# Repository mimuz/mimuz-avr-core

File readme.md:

# mi:muz avr-core

`mi:muz avr-core`はATtiny向けのArduino用MIDIライブラリです。

------

## Arduino Library

Arduinoを使ってMIDIで遊ぶためのATtinyにMIDI機能を追加するライブラリとArduino IDE 1.6.3向けの設定ファイル。

- [VUSB-MIDI-ATtiny](./arduino/libraries/VUSBMidiATtiny)（ATtinyでUSB-MIDIデバイスを作るためのArduinoライブラリ）
- [ArduinoIDE 1.6.3向け設定ファイル](./arduino/hardware)（Arduino IDEにmi:muzボード設定を追加するファイル）
- [Hybrid MIDI for mi:muz:expr](./arduino/libraries/HybridMidiAttiny) (mi:muz:exprボード用のArduinoライブラリ。V-USBとI2C Slaveの両方に対応したMIDIデバイスが作れます)

## boards

mi:muz avr-coreに対応したボードの回路図とサンプルコードです

### mi:muz ATtiny Boards (protシリーズ)

ATtinyを搭載しV-USB MIDIを使ったMIDIデバイスを簡単に作るための実験用ボード。

- [mi:muz:prot#1](./boards/prot1)（ATtiny45/85用V-USB-MIDI実験用ボード）
- [mi:muz:prot#2](./boards/prot2)（ATtiny44/84/841用V-USB-MIDI実験用ボード）
- [mi:muz:prot#3](./boards/prot3)（ATtiny45/85用V-USB-MIDI実験用ボード。I2Cマスタ用回路入り）

### mi:muz ATtiny Boards (exprシリーズ)

ATtinyを搭載しHybrid MIDIに対応したMIDIデバイスを簡単に作るための実験用ボード。
Arduinoと複数のexprシリーズボードを組み合わせた実験が行いたいときはこちら。

- [mi:muz:expr#1](./boards/expr1)（ATtiny85用Hybrid-MIDI実験用ボード）
- [mi:muz:expr#2](./boards/expr2)（ATtiny841用Hybrid-MIDI実験用ボード）

### Arduinoシールド

mi:muzを有効活用するためのArduino UNO用シールド。

- [mi:muz:wrtr](./boards/wrtr)（8/14ピンATtiny向けの小さなISPシールド）
- [mi:muz:mstr-uno](./boards/mstr-uno) (mi:muz:exprをArduino UNOに接続するためのシールド)

### mi:muz ATtinyボード用アタッチメント

mi:muz ATtinyボードを使って簡単にデバイスの実験を行うためのアタッチメント。

- [mi:muz:sndr#1](./boards/sndr1)（mi:muz:expr#1,#2用オーディオアダプタ）
- [mi:muz:ctlr#1](./boards/ctlr1)（mi:muz:expr#2用 8chコントローラーアダプタ）

# Applications

`mi:muz`プロジェクトで生まれたデバイスを紹介しています。

- [フィジカルWebアプリ「ち〜ん」](http://qiita.com/tadfmac/items/702e74efad1dd606166a)（MIDIデバイス化した呼び鈴と連携するWebアプリ）
- [mi:muz:can (旧名：can attacker (缶たたくやつ))](https://github.com/mimuz/mimuz-can)
- [mi:muz:tuch](https://github.com/mimuz/mimuz-tuch) MIDI Controller with flexible touch keys.

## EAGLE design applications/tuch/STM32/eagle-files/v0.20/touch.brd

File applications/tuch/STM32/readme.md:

# mi:muz:tuch (MIDI Controller with flexible touch keys) STM32 Version

mi:muz:tuch is a USB MIDI controller with capacitive touch sensor.
It has now two indivisual versions, AVR or STM32.

And also, Web preset configurator is available to [Configurator](http://mz4u.net/tuch/).
MIDI note numbers be able to change to You want.  

# STM32 Version (STM32F042K6T6)

STM32 version of mi:muz:tuch (v0.2x) is my first STM32 project, it now only support USB Mode.

## Version

- v0.20 (2016.08.27)

## Known Issues

- v0.20 does not support I2C Slave Mode.

## Schematic

## Top View

## Eagle Files

[eagle files (v0.20)](./eagle-files/v0.20)

## parts

- [STM32F042K6T6](http://www.st.com/content/st_com/ja/products/microcontrollers/stm32-32-bit-arm-cortex-mcus/stm32f0-series/stm32f0x2/stm32f042k6.html) * 1
- [Ferrite beads](http://akizukidenshi.com/catalog/g/gP-04054/) * 2 [ID1,ID2]
- 470Ω(0603) * 1 (For USB DATA LED)
- 1kΩ(0603) * 6 (For touch line LED)
- 1.5kΩ(0603) * 1 (D+ Line Pull up)
- 10kΩ(0603) * 1 (Tactical switch pull down)
- 1MΩ(2012) * 6 (For Touch Sensor)
- 3mLED * 7 
- 0.1uF(0603) * 4
- 22uF(0805) * 1
- [Tactical Switch (4 points SMT 4.5mm)](http://www.aitendo.com/product/7047) * 1
- [Tactical Switch (2 points SMT)](http://www.aitendo.com/product/10525) * 1

## Firmware

- [Source](./source)
- [bin](./bin)

### Firmware Setup 

1. Install [SW4STM32](http://www.st.com/content/st_com/ja/products/development-tools/software-development-tools/stm32-software-development-tools/stm32-ides/sw4stm32.html)
2. Install DFU Loader (i.e. dfu-util see [dfu-util - Device Firmware Upgrade Utilities](http://dfu-util.sourceforge.net/))
2. Copy [Source](./source/mimuz-tuch) to your workspace path and Bulding Software
3. Connect mi:muz:tuch board with holding push to 'BOOT0' Switch to USB Port
4. Burn [mimuz-tuch.bin] using DFU Loader. On Mac, enter the following command on shell in same mimuz-tuch.bin path.

> `dfu-util -a0 -d 0x0483:0xdf11 -s 0x008000000 -D mimuz-tuch.bin`

# Licenses

## Hardware (Schematics, Board, Eagle files), Software (Application, USB-MIDI Class Driver)

- [Creative Commons Attribution 4.0 International (CC BY 4.0)](http://creativecommons.org/licenses/by/4.0/)

## Software (STMCube from ST Microsystems)

- 3-clause BSD license

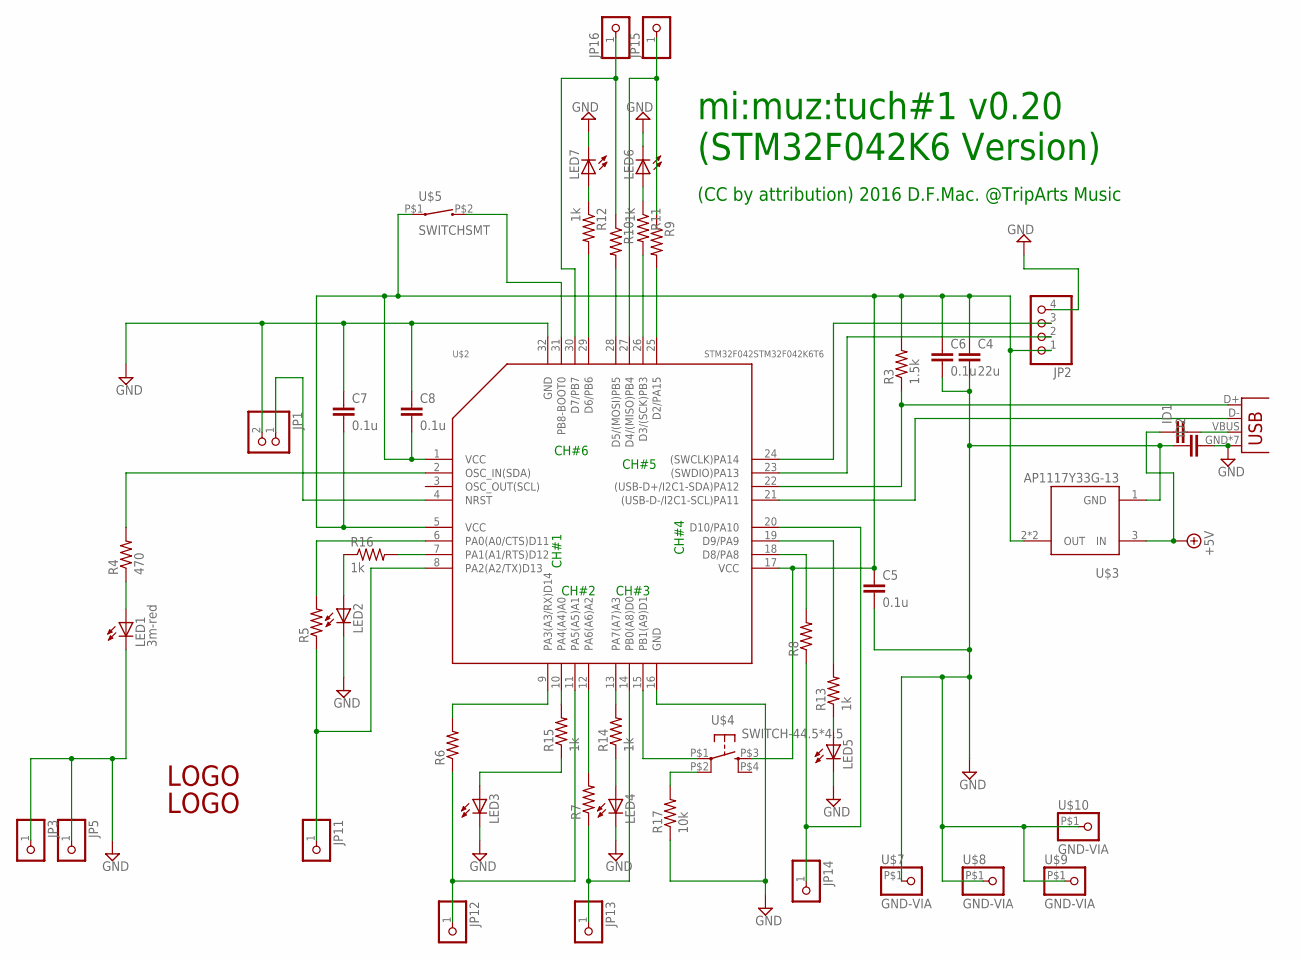
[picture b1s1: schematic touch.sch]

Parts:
C4: 22u; C0805
C5, C6, C7, C8: 0.1u; C0603
ID1, ID2: C-EUC0805; C0805
JP1: PINHD-1X2; 1X02
JP2: PINHD-1X4; 1X04
JP3, JP5: PINHD-1X13MM; 1X01
JP4: USB-MICROB
JP11, JP12, JP13, JP14, JP15, JP16: PINHD-1X15MM; 1X01-LARGE
LED1: 3m-red; LED3MM
LED2, LED3, LED4, LED5, LED6, LED7: LED3MM
R3: 1.5k; R0603
R4: 470; R0603
R5, R6, R7, R8, R9, R10: R-US_R0805; R0805
R11, R12, R13, R14, R15, R16: 1k; R0603
R17: 10k; R0603
U$1, U$6: LOGOSMALL; LOGO-SMALL
U$2: STM32F042STM32F042K6T6; TQFP32
U$3: AP1117Y33G-13; SOT89
U$4: SWITCH-44.5*4.5; SWITCH-SMT-4.5*4.5
U$5: SWITCHSMT; SWITCH-SMT-2*4*3
U$7, U$8, U$9, U$10: GND-VIA

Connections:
+5V: ID1.1, U$3.3 (IN)
D+: JP4.D+, R3.1, U$2.22 ((USB-D+/I2C1-SDA)PA12)
D-: JP4.D-, U$2.21 ((USB-D-/I2C1-SCL)PA11)
GND: C4.2, C5.2, C6.2, C7.1, C8.1, ID2.1, ID2.2, JP1.2, JP2.4, JP3.1, JP4.GND, JP4.MT1 (GND), JP4.MT3 (GND), JP4.P$2 (GND), JP4.P$4 (GND), JP4.P$5 (GND), JP4.P$6 (GND), JP5.1, LED1.K (C), LED2.K (C), LED3.K (C), LED4.K (C), LED5.K (C), LED6.K (C), LED7.K (C), R17.1, U$2.16 (GND), U$2.32 (GND), U$3.1 (GND), U$7.P$1, U$8.P$1, U$9.P$1, U$10.P$1
unnamed: R5.2, U$2.6 (PA0(A0/CTS)D11)
unnamed: R4.2, U$2.2 (OSC_IN(SDA))
unnamed: R15.2, U$2.10 (PA4(A4)A0)
unnamed: R16.2, U$2.7 (PA1(A1/RTS)D12)
unnamed: LED3.A, R15.1
unnamed: LED1.A, R4.1
unnamed: R14.2, U$2.13 (PA7(A7)A3)
unnamed: R17.2, U$4.P$2 (P1)
unnamed: JP11.1, R5.1, U$2.8 (PA2(A2/TX)D13)
unnamed: R6.2, U$2.9 (PA3(A3/RX)D14)
unnamed: R8.2, U$2.18 (D8/PA8)
unnamed: R13.2, U$2.19 (D9/PA9)
unnamed: R7.2, U$2.12 (PA6(A6)A2)
unnamed: R9.2, U$2.25 (D2/PA15)
unnamed: C4.1, C5.1, C6.1, C7.2, C8.2, JP2.1, R3.2, U$2.1 (VCC), U$2.5 (VCC), U$2.17 (VCC), U$3.2 (OUT), U$3.2@1 (OUT), U$4.P$3 (S), U$5.P$1 (1)
unnamed: R11.2, U$2.26 (D3/(SCK)PB3)
unnamed: R10.2, U$2.28 (D5/(MOSI)PB5)
unnamed: R12.2, U$2.29 (D6/PB6)
unnamed: U$2.15 (PB1(A9)D1), U$4.P$1
unnamed: LED2.A, R16.1
unnamed: LED7.A, R12.1
unnamed: LED6.A, R11.1
unnamed: LED4.A, R14.1
unnamed: LED5.A, R13.1
unnamed: JP2.3, U$2.24 ((SWCLK)PA14)
unnamed: JP2.2, U$2.23 ((SWDIO)PA13)
unnamed: JP1.1, U$2.4 (NRST)
unnamed: U$2.31 (PB8-BOOT0), U$5.P$2 (2)
unnamed: JP12.1, R6.1, U$2.11 (PA5(A5)A1)
unnamed: JP13.1, R7.1, U$2.14 (PB0(A8)D0)
unnamed: JP14.1, R8.1, U$2.20 (D10/PA10)
unnamed: JP15.1, R9.1, U$2.27 (D4/(MISO)PB4)
unnamed: JP16.1, R10.1, U$2.30 (D7/PB7)
VBUS: ID1.2, JP4.VBUS

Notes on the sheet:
mi:muz:tuch#1 v0.20 (STM32F042K6 Version)
(CC by attribution) 2016 D.F.Mac. @TripArts Music
CH#1
CH#2
CH#3
CH#4
CH#5
CH#6

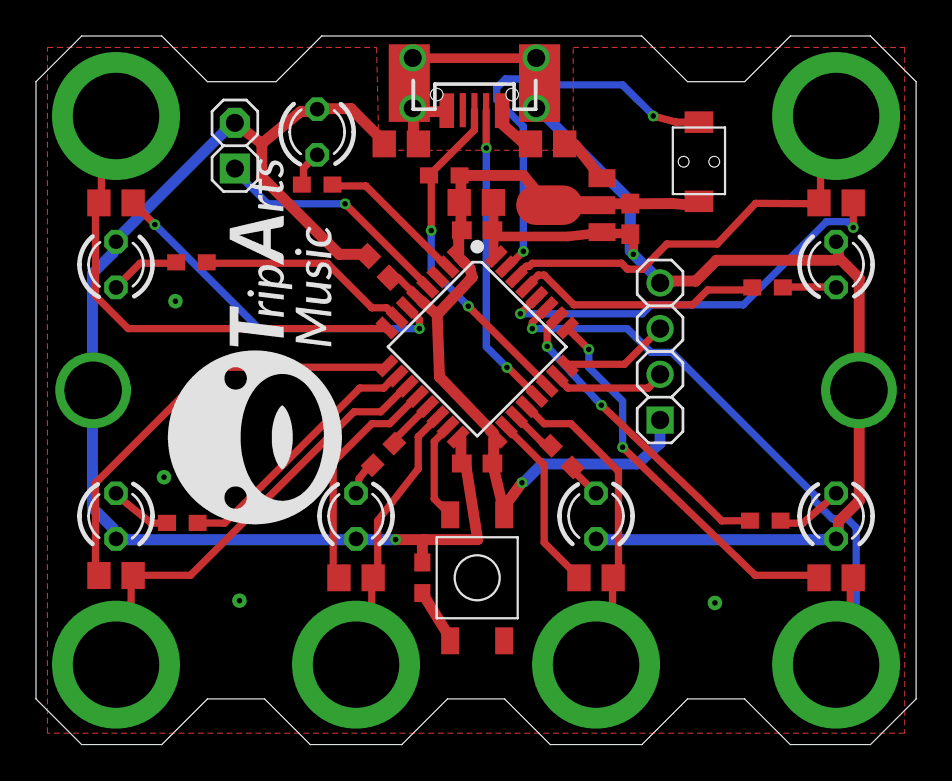
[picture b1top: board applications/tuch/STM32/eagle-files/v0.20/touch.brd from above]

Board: 2 copper layers, 48.9 x 39.4 mm, 50 parts (1 on the bottom side), 38 nets.

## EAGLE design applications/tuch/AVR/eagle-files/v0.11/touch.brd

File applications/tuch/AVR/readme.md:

# mi:muz:tuch (MIDI Controller with flexible touch keys) AVR Version

mi:muz:tuch is a USB MIDI controller with capacitive touch sensor.
It has now two indivisual versions, AVR or STM32.

And also, Web preset configurator is available to [Configurator](http://mz4u.net/tuch/).
MIDI note numbers be able to change to You want.  

# AVR Version (ATtiny44 16Mhz with ATmega8A 8Mhz)

AVR version of mi:muz:tuch (v0.1x) is based mi:muz:expr#2 for 'Hybrid MIDI feature, It can be able to connect to PC's USB Port using V-USB or mi:muz:mstr (I2C master) devices's I2C port using I2C slave mode.

## Version

- v0.11 (2016.07.31)

## Known Issues

- v0.1x does not work properly when connected to a USB2.0 Hub. (V-USB's general issue... unfixable...)
- [v0.1x does not work USB Mode when ch#6 is enable.] (https://github.com/tadfmac/mi-muz/issues/4)

## Schematic

## Top View

## Bottom View

## Eagle Files

[eagle files (v0.11)](./eagle-files/v0.11)

## parts

- [ATtiny44A-SSU](http://www.atmel.com/ja/jp/devices/ATTINY44A.aspx) * 1
- [ATmega8A-AU](http://www.atmel.com/ja/jp/devices/ATMEGA8A.aspx) * 1
- Zener diode(SOD323) 3.6V * 2
- Crystal 16Mhz (5032 2Pad) * 1
- [Ferrite beads](http://akizukidenshi.com/catalog/g/gP-04054/) * 2 [ID1,ID2]
- 100Ω(0603) * 2 (For USB D+, D- Line)
- 470Ω(0603) * 1 (For ATtiny44 LED)
- 1kΩ(0603) * 6 (For ATmega8A touch line LED)
- 4.7kΩ(0603) * 1 (D- Line Pull up)
- 10kΩ(0603) * 1 (Tactical switch pull down)
- 1MΩ(2012) * 6 (For Touch Sensor)
- 3mLED * 7 
- 22pF(0603) * 2
- 0.1uF(0603) * 5
- 22uF(0805) * 1
- [Switch](http://akizukidenshi.com/catalog/g/gP-03651/) * 1
- Pin headers (2.54mm) 2×3 * 2
  WARNING: if you have v0.1 board, it has a bug that missing junction from ATmega8A to ISP.

## sketches

- [Touch Sensor (for ATmega8A)](https://github.com/tadfmac/mi-muz/tree/master/applications/tuch/sketch/mega8_touchSensor/)
- [Touch Sensor to Hybrid MIDI bridge (for ATtiny44A)](https://github.com/tadfmac/mi-muz/tree/master/applications/tuch/sketch/mimuz-tuch_v01/)

# Licenses

## Hardware (Schematics), Configurator

[Creative Commons Attribution 4.0 International (CC BY 4.0)](http://creativecommons.org/licenses/by/4.0/)

## Software (Sketches/Libraries)

[GNU General Public License, version 2 (GPL-2.0)](http://opensource.org/licenses/gpl-2.0.php).

See lso [HybridMidiAttiny](https://github.com/tadfmac/mi-muz/tree/master/arduino/libraries/HybridMidiAttiny).

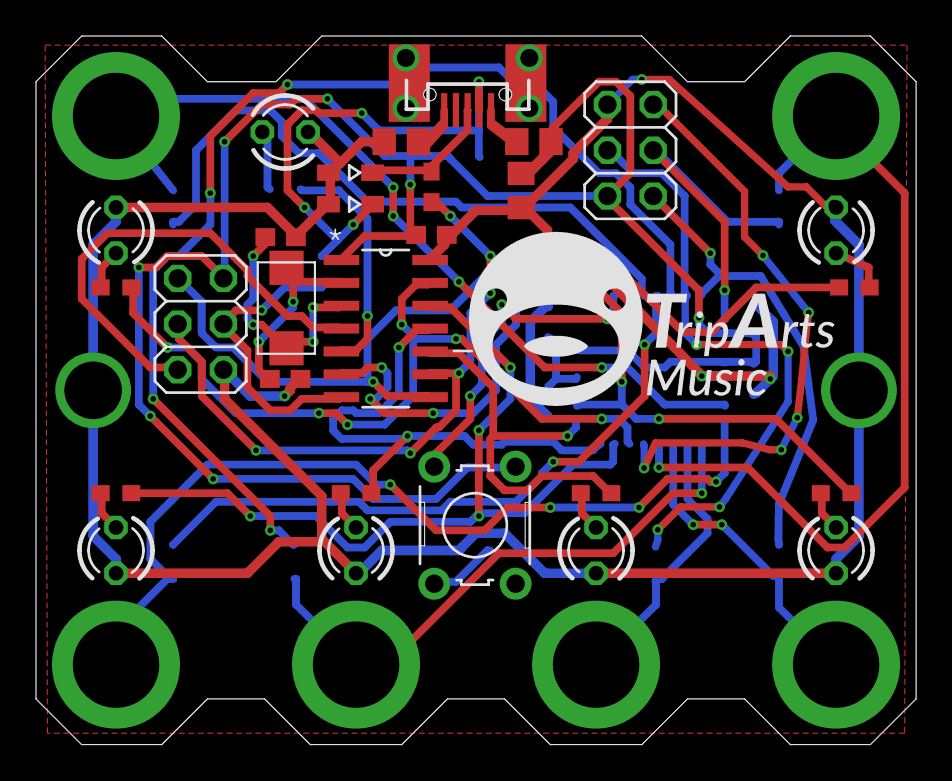
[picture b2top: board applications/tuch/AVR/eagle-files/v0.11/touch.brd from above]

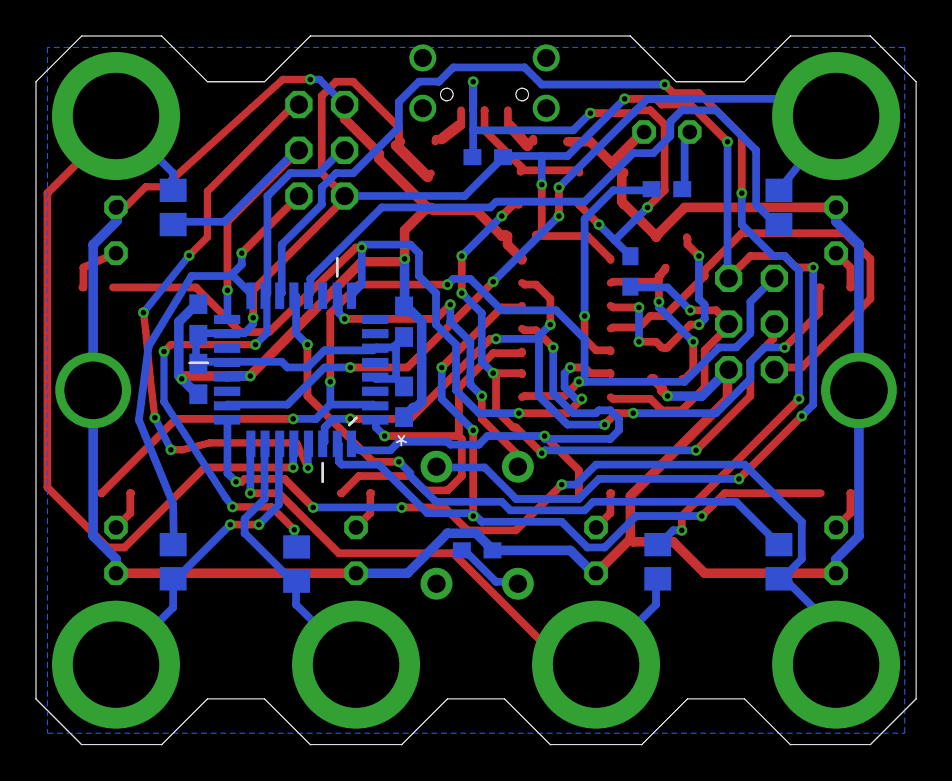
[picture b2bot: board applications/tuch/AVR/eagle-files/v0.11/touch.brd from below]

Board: 2 copper layers, 48.9 x 39.4 mm, 52 parts (15 on the bottom side), 40 nets.

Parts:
C1, C5, C6, C7, C8: 0.1u; C0603
C2, C3: 22p; C0603
C4: 22u; C0805
ID1, ID2: C0805
JP1, JP2: 2X03
JP3, JP5: 1X01
JP4: USB-MICROB
JP11, JP12, JP13, JP14, JP15, JP16: 1X01-LARGE
LED1: 3m-red; LED3MM
LED2, LED3, LED4, LED5, LED6, LED7: LED3MM
Q1: MC-405
R1, R2, R17: 75; R0603
R3: 1.5k; R0603
R4, R11, R12, R13, R14, R15, R16: 470; R0603
R5, R6, R7, R8, R9, R10: R0805
S1: B3F-10XX
U2: ATTINY44-20SSU; SOIC127P600X175-14N
U3: ATMEGA8A-AU; QFP80P900X900X120-32N
U$1: LOGOSMALL; LOGO-SMALL
ZD1, ZD2: 3.6V; SOD323-W

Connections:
+5V: C1.1, C4.1, C5.1, C6.1, C7.1, C8.1, ID1.1, JP1.2, JP2.2, R3.2, S1.1, U2.1, U3.4, U3.6, U3.18, U3.20
D+: JP4.D+, R2.2, ZD1.C
D-: JP4.D-, R1.2, R3.1, ZD2.C
GND: C1.2, C2.1, C3.1, C4.2, C5.2, C6.2, C7.2, C8.2, ID2.1, JP1.6, JP2.6, JP3.1, JP5.1, LED1.K, LED2.K, LED3.K, LED4.K, LED5.K, LED6.K, LED7.K, R17.1, U2.14, U3.21, ZD1.A, ZD2.A
GND1: ID2.2, JP4.GND
unnamed: R5.2, U3.12
unnamed: R4.2, U2.5
unnamed: C2.2, Q1.2, U2.2
unnamed: C3.2, Q1.1, U2.3
unnamed: R11.2, U2.13, U3.30
unnamed: LED1.A, R4.1
unnamed: R12.2, U2.12, U3.31
unnamed: R14.2, U2.10, U3.1
unnamed: JP11.1, R5.1, U3.23
unnamed: JP2.5, U2.4
unnamed: R13.2, U2.11, U3.32
unnamed: JP2.4, R1.1, U2.7
unnamed: R6.2, U3.13
unnamed: R17.2, S1.4
unnamed: R7.2, U3.14
unnamed: JP1.4, R8.2, U3.15
unnamed: JP1.5, U3.29
unnamed: JP1.1, R9.2, U3.16
unnamed: JP1.3, R10.2, U3.17
unnamed: LED7.A, R16.1
unnamed: LED6.A, R15.1
unnamed: LED5.A, R14.1
unnamed: LED4.A, R13.1
unnamed: LED3.A, R12.1
unnamed: LED2.A, R11.1
unnamed: R16.2, U2.6, U3.9
unnamed: JP12.1, R6.1, U3.24
unnamed: JP13.1, R7.1, U3.25
unnamed: JP14.1, R8.1, U3.26
unnamed: JP15.1, R9.1, U3.27
unnamed: JP16.1, R10.1, U3.28
unnamed: S1.3, U3.10
unnamed: JP2.3, R2.1, U2.9
unnamed: JP2.1, R15.2, U2.8, U3.2
VBUS: ID1.2, JP4.VBUS

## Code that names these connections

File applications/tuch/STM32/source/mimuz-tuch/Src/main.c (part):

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//
// PIN Configuration
//
// PA0 : CH#1 Sensor (OUT)
// PA1 : CH#1 LED    (OUT)
// PA2 : CH#1 Sensor (IN)
// PA3 : CH#2 Sensor (OUT)
// PA4 : CH#2 LED    (OUT)
// PA5 : CH#2 Sensor (IN)
// PA6 : CH#3 Sensor (OUT)
// PA7 : CH#3 LED    (OUT)
// PB0 : CH#3 Sensor (IN)
// PB1 : Calibration Button (IN)
// PA8 : CH#4 Sensor (OUT)
// PA9 : CH#4 LED    (OUT)
// PA10: CH#4 Sensor (IN)
// PA11: USB D-
// PA12: USB D+
// PA13: SWDIO
// PA14: SWCLK
// PA15: CH#5 Sensor (OUT)
// PB3 : CH#5 LED    (OUT)
// PB4 : CH#5 Sensor (IN)
// PB5 : CH#6 Sensor (OUT)
// PB6 : CH#6 LED    (OUT)
// PB7 : CH#6 Sensor (IN)
// PB8 : BOOT0
// PF0 : USB DATA LED (OUT)
// PF1 : N/A

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
// Tuch Sensor GPIO Table
TTouchGPIO ttouchGpio[TOUCH_CHANNELS]={
  {GPIOA, GPIOA, GPIOA, GPIO_PIN_0, GPIO_PIN_1, GPIO_PIN_2}, // PA0, PA1, PA2 (CH#1)
  {GPIOA, GPIOA, GPIOA, GPIO_PIN_3, GPIO_PIN_4, GPIO_PIN_5}, // PA3, PA4, PA5 (CH#2)
  {GPIOA, GPIOA, GPIOB, GPIO_PIN_6, GPIO_PIN_7, GPIO_PIN_0}, // PA6, PA7, PB0 (CH#3)
  {GPIOA, GPIOA, GPIOA, GPIO_PIN_8, GPIO_PIN_9, GPIO_PIN_10},// PA8, PA9, PA10(CH#4)
  {GPIOA, GPIOB, GPIOB, GPIO_PIN_15,GPIO_PIN_3, GPIO_PIN_4}, // PA15,PB3, PB4 (CH#5)
  {GPIOB, GPIOB, GPIOB, GPIO_PIN_5, GPIO_PIN_6, GPIO_PIN_7}  // PB5, PB6, PB7 (CH#6)
};

void sensorLEDOn(int ch){
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

// GPIO PIN Configuration
// PA0 : CH#1 Sensor (OUT)
// PA1 : CH#1 LED    (OUT)
// PA2 : CH#1 Sensor (IN)
// PA3 : CH#2 Sensor (OUT)
// PA4 : CH#2 LED    (OUT)
// PA5 : CH#2 Sensor (IN)
// PA6 : CH#3 Sensor (OUT)
// PA7 : CH#3 LED    (OUT)
// PB0 : CH#3 Sensor (IN)
// PB1 : Calibration Button (IN)
// PA8 : CH#4 Sensor (OUT)
// PA9 : CH#4 LED    (OUT)
// PA10: CH#4 Sensor (IN)
// PA11: USB D-
// PA12: USB D+
// PA13: SWDIO
// PA14: SWCLK
// PA15: CH#5 Sensor (OUT)
// PB3 : CH#5 LED    (OUT)
// PB4 : CH#5 Sensor (IN)
// PB5 : CH#6 Sensor (OUT)
// PB6 : CH#6 LED    (OUT)
// PB7 : CH#6 Sensor (IN)
// PB8 : BOOT0
// PF0 : USB DATA LED (OUT)
// PF1 : N/A

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  GPIO_InitStruct.Speed = GPIO_SPEED_FREQ_LOW;
  HAL_GPIO_Init(GPIOF, &GPIO_InitStruct);

  /*Configure GPIO pins : PA0 PA1 PA3 PA4 
                           PA6 PA7 PA8 PA9 
                           PA15 */
  GPIO_InitStruct.Pin = GPIO_PIN_0|GPIO_PIN_1|GPIO_PIN_3|GPIO_PIN_4 
                          |GPIO_PIN_6|GPIO_PIN_7|GPIO_PIN_8|GPIO_PIN_9 
                          |GPIO_PIN_15;
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  GPIO_InitStruct.Speed = GPIO_SPEED_FREQ_LOW;
  HAL_GPIO_Init(GPIOA, &GPIO_InitStruct);

  /*Configure GPIO pins : PA2 PA5 PA10 */
  GPIO_InitStruct.Pin = GPIO_PIN_2|GPIO_PIN_5|GPIO_PIN_10;
  GPIO_InitStruct.Mode = GPIO_MODE_INPUT;
  GPIO_InitStruct.Pull = GPIO_NOPULL;
  HAL_GPIO_Init(GPIOA, &GPIO_InitStruct);

  /*Configure GPIO pins : PB0 PB1 PB4 PB7 */
  GPIO_InitStruct.Pin = GPIO_PIN_0|GPIO_PIN_1|GPIO_PIN_4|GPIO_PIN_7;
  GPIO_InitStruct.Mode = GPIO_MODE_INPUT;
  GPIO_InitStruct.Pull = GPIO_NOPULL;
  HAL_GPIO_Init(GPIOB, &GPIO_InitStruct);

  /*Configure GPIO pins : PB3 PB5 PB6 */
  GPIO_InitStruct.Pin = GPIO_PIN_3|GPIO_PIN_5|GPIO_PIN_6;
  GPIO_InitStruct.Mode = GPIO_MODE_OUTPUT_PP;
  GPIO_InitStruct.Pull = GPIO_NOPULL;
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
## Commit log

2014-10-13 add sendNoteOff, sendCtlChange
2014-10-13 change readme.md and add schema.png
2014-10-13 change readme.md
2014-12-14 enable wdt reset on sendMidiMessage
2014-12-14 add cheen sounder to example
2014-12-14 add example description to readme.md
2014-12-14 fix readme.md
2014-12-29 support ATTiny44/84
2014-12-29 add comment
2015-01-22 add cheen schematic
2015-04-27 support t841, etc.
2015-04-28 change directories
2015-04-28 add hardware folder
2015-04-28 rename
2015-04-28 rename2
2015-04-28 readme.md and title rewrite
2015-04-28 change title
2015-04-29 change directory
2015-04-29 move files
2015-04-29 add wrtr
2015-04-29 add readme.md
2015-04-29 add logo
2015-04-29 wrtr:add parts list
2015-04-29 Deleted: .DS_Store, Added: .gitignore
2015-04-29 /DS_Store banished
2015-04-29 wow...
2015-04-29 wrtr: add arduino pin number to schematic
2015-04-29 prot3: add readme.md and schematic
2015-04-29 readme.md add prot3 link
2015-04-29 boards: add prot2
2015-04-29 readme.md: add application desc
2015-04-29 readme.md: mod application desc
2015-04-29 wrtr: add image
2015-04-29 wrtr: mod desc
2015-04-29 prot2: add image
2015-04-29 readme.md: fix typo
2015-04-29 readme.md: fix typo again..]
2015-04-29 vusb-midi-attiny: readme.md wip
2015-04-30 prot3:fix capacity C2
2015-04-30 readme.md: fix applications desc
2015-04-30 wrtr: add example
2015-04-30 VUSBMidiATtiny:example:sounder bug fix
2015-04-30 board.txt comment
2015-04-30 VUSBMidiATtiny:examples:sounder bug fixed
2015-04-30 arduino/hardware/mimuz add platform.txt and fix board.txt
2015-05-01 prot3: add example and image
2015-05-03 add attiny841 support files
2015-05-05 prot3: add pin mapping
2015-05-05 VUSBMidiATtiny:example:blink: to Arduino friendly
2015-05-05 VUSBMidiATtiny:example new example controller
2015-05-05 VUSBMidiATtiny:example:controller fix pin number
2015-05-05 tiny14/pins_arduino.h: fix timer pin mapping
2015-05-06 VUSBMidiATtiny/example/sounder: add experimental support ATtiny84/44 tiny841 is not yet.
2015-05-06 VUSBMidiATtiny/example/sounder: fix header comment.
2015-05-07 many changes for ATtiny841
2015-05-08 VUSBMidiATtiny:performance improved
2015-05-08 VUSBMidiATtiny/example/sounder fix verbose oscillator..
2015-05-17 fix USB voltage definition in usbconfig.h
2015-05-23 add prot#1 board info
2015-05-23 VUSBMidiATtiny: change directory
2015-05-23 VUSBMidiATtiny/readme.md: add desc for controller
2015-05-25 add expr#1 support
2015-05-25 rm rhythmer due to this sample WIP now
2015-05-29 VUSBMidiATtiny:MimuzHelper.h add pinMode(INPUT_PULLUP) support for ATtiny441/841
2015-06-24 add HybridMidiATtiny
2015-06-24 HybridMidiATtiny:example add blink_h, button_h, controller_h and sounder_h
2015-06-25 add boards expr1, expr2, sndr1
2015-06-25 readme.md add board information
2015-07-04 boards/expr1,expr2 fix R3 registor value 1.5K to 4.7K
2015-07-24 add images to expr1 and expr2
2015-07-24 rename image files
2015-07-24 readme.md:add board info
2015-07-24 add board mstr:uno
2015-07-24 readme.md: fix board mstr:uno
2015-07-24 boards:mstr:uno readme.md: fix
2015-07-24 boards:sndr add image
2015-08-25 add application folder with can attacker informations
2015-08-25 readme.md: add link to can attacker
2015-08-30 applications:canattacker: add arduino UNO Version
2015-08-30 applications:canattacker: fix comment
2015-09-04 boards:ctlr1:fix readme.md
2015-09-12 Now supported SPI feature on ATtiny841/441 to REMAPed SPI PINs.
2015-11-24 applications:canattacker: add arduino leonardo version
2015-11-24 applications:canattacker: add photo
2016-03-26 add partial support ATmega328P board : mi:muz:expr-mega#P1
2016-05-11 fix board.txt
2016-05-29 partial support for board: BrushKnob v1
2016-05-29 VUSBMidiATtiny:readme.md add example desc
2016-08-01 add board mi:muz:tuch
2016-08-01 tuch folder move to applications
2016-08-01 rename device-small.png to device.png
2016-08-01 add issue number
2016-08-01 readme.md add link tuch link
2016-08-01 readme.md fix usage
2016-08-01 readme.md: fix link to sketch
2016-08-01 add schematic, board images
2016-08-02 tuch:readme.md add parts list
2016-08-03 readme.md lazy poor english
2016-08-03 add board photo (v0.1)
2016-08-03 tuch: photo change png to jpeg
2016-08-24 add eagle files
2016-08-27 add stm32 to this project
2016-08-27 [mi:muz:tuch] add stm32 version
2016-08-27 fix path
2016-08-27 add readme.md to stm32
2016-08-27 add USB VID/PID comment
2016-08-27 [mi:muz:tuch]add STM32 bin file
2016-09-05 mi:muz:tuch(stm32) fix touch sensor bug
2016-09-06 mi:muz:tuch fix USBdesc
2016-09-06 mi:muz:tuch disable internal pullup for DP
2016-09-12 mi:muz:tuch/configurator add wk files
2016-09-20 fix source link
2017-05-02 remove applications folder
2017-05-02 remove
2017-08-07 avrdude.conf: add support ATtiny441
